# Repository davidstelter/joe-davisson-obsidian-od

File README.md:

Joe Davisson Obsidian Overdrive
===============================

Original design Copyright © 2009 Joe Davisson.
Schematic from [AnalogAlchemy](http://www.diystompboxes.com/analogalchemy/sch/obsidian.html)

I'm just drawing this out to create a PCB for myself. Original work here is licensed under Creative Commons, use it if it's useful to you.

Original content from Joe:

Obsidian
--------
This distortion unit uses three MOSFET gain stages followed by a simple Big-Muff style tone control. It is a positive-ground circuit, so it should be powered with a battery. It doesn't draw much power anyway.
It's important to build the circuit on a breadboard first, as the MOSFETs will usually require re-biasing. Adjust the 3.9k resistors until the drains are at approximately 4.5v. This doesn't have to be exact, anywhere between 4-5 volts is fine.

The circuit may also be built in a normal negative-ground configuration, using 2N7000 or BS170 devices. However, there will be a higher level of background noise.

Copyright © 2009 Joe Davisson. All Rights Reserved.

Preview
-------

Parts Libs
----------
Don't know how these work with regards to embedding in an Eagle schematic or board... so linking to them to avoid losing track.
[MusicThingModular.lbr](https://raw.githubusercontent.com/TomWhitwell/MTM-Parts-Library/master/MusicThingModular.lbr)
[audio.lbr](https://raw.githubusercontent.com/robertstarr/lbr_user/master/audio.lbr)

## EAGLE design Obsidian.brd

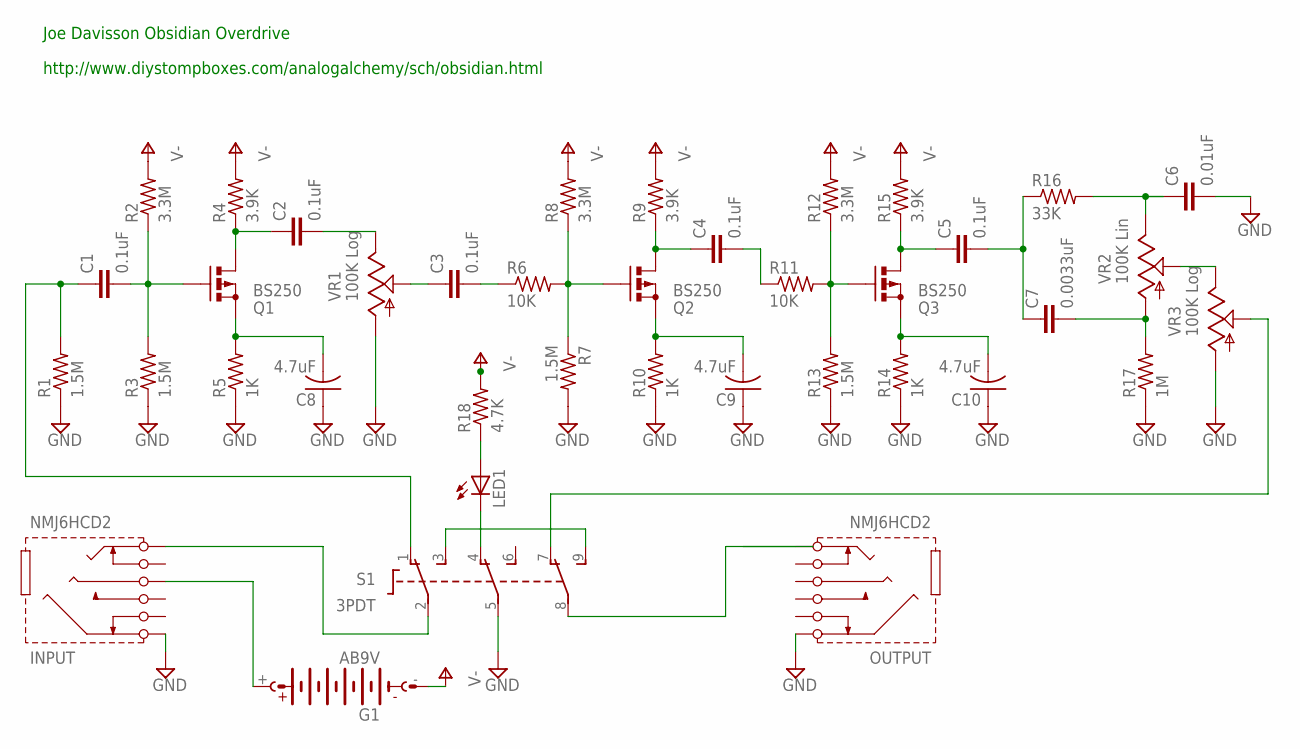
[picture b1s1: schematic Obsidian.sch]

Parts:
C1, C2, C3, C4, C5: 0.1uF; C5B4.5
C6: 0.01uF; C5B4.5
C7: 0.0033uF; C5B4.5
C8, C9, C10: 4.7uF; C025-025X050
G1: AB9V
INPUT: NMJ6HCD2
LED1: LED5MM
OUTPUT: NMJ6HCD2
Q1, Q2, Q3: BS250; SOT54E
R1, R3, R7, R13: 1.5M; 0207/7
R2, R12: 3.3M; 0204/7
R4: 3.9K; 0207/7
R5: 1K; 0207/7
R6: 10K; 0207/7
R8: 3.3M; 0207/7
R9, R15: 3.9K; 0204/7
R10, R14: 1K; 0204/7
R11: 10K; 0204/7
R16: 33K; 0204/7
R17: 1M; 0204/7
R18: 4.7K; 0204/7
S1: 3PDT
VR1, VR3: 100K Log; 9MM_SNAP-IN_POT
VR2: 100K Lin; 9MM_SNAP-IN_POT

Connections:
GND: C6.2, C8.1, C9.1, C10.1, INPUT.S (SLEEVE), OUTPUT.S (SLEEVE), R1.1, R3.1, R5.1, R7.2, R10.1, R14.1, R17.1, S1.5 (P2), VR1.1 (A)
unnamed: C2.1, Q1.D, R4.1
unnamed: C8.2, Q1.S, R5.2
unnamed: C1.2, Q1.G, R2.1, R3.2
unnamed: Q2.G, R6.2, R7.1, R8.1
unnamed: C1.1, R1.2, S1.1 (O1)
unnamed: C3.2, R6.1
unnamed: C9.2, Q2.S, R10.2
unnamed: C5.1, Q3.D, R15.1
unnamed: C4.1, Q2.D, R9.1
unnamed: C10.2, Q3.S, R14.2
unnamed: Q3.G, R11.2, R12.1, R13.2
unnamed: C4.2, R11.1
unnamed: C2.2, VR1.3 (E)
unnamed: C6.1, R16.2, VR2.3 (E)
unnamed: C3.1, VR1.2 (S)
unnamed: C5.2, C7.1, R16.1
unnamed: C7.2, R17.2, VR2.1 (A)
unnamed: VR2.2 (S), VR3.3 (E)
unnamed: S1.7 (O3), VR3.2 (S)
unnamed: G1.+, INPUT.R (RING)
unnamed: LED1.K (C), S1.4 (O2)
unnamed: INPUT.T (TIP), S1.2 (P1)
unnamed: S1.3 (S1), S1.9 (S3)
unnamed: LED1.A, R18.1
V-: G1.-, R2.2, R4.2, R8.2, R9.2, R12.2, R15.2

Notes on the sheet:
Joe Davisson Obsidian Overdrive
http://www.diystompboxes.com/analogalchemy/sch/obsidian.html

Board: 2 copper layers, 39 parts (0 on the bottom side), 26 nets, no tracks yet.

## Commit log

2017-08-21 Initial commit, no board design.
2017-08-21 Added preview image of schematic
2017-08-22 Update README, .gitignored eagle revision(?) files
2017-08-22 Found parts libs for pots, jacks, etc!
2017-08-22 Start of 1590BB PCB
    Not much layout done, no real dimensions yet either.

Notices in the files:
parts and their libraries:
audio: Copyright (C) 2008, Bob Starr
